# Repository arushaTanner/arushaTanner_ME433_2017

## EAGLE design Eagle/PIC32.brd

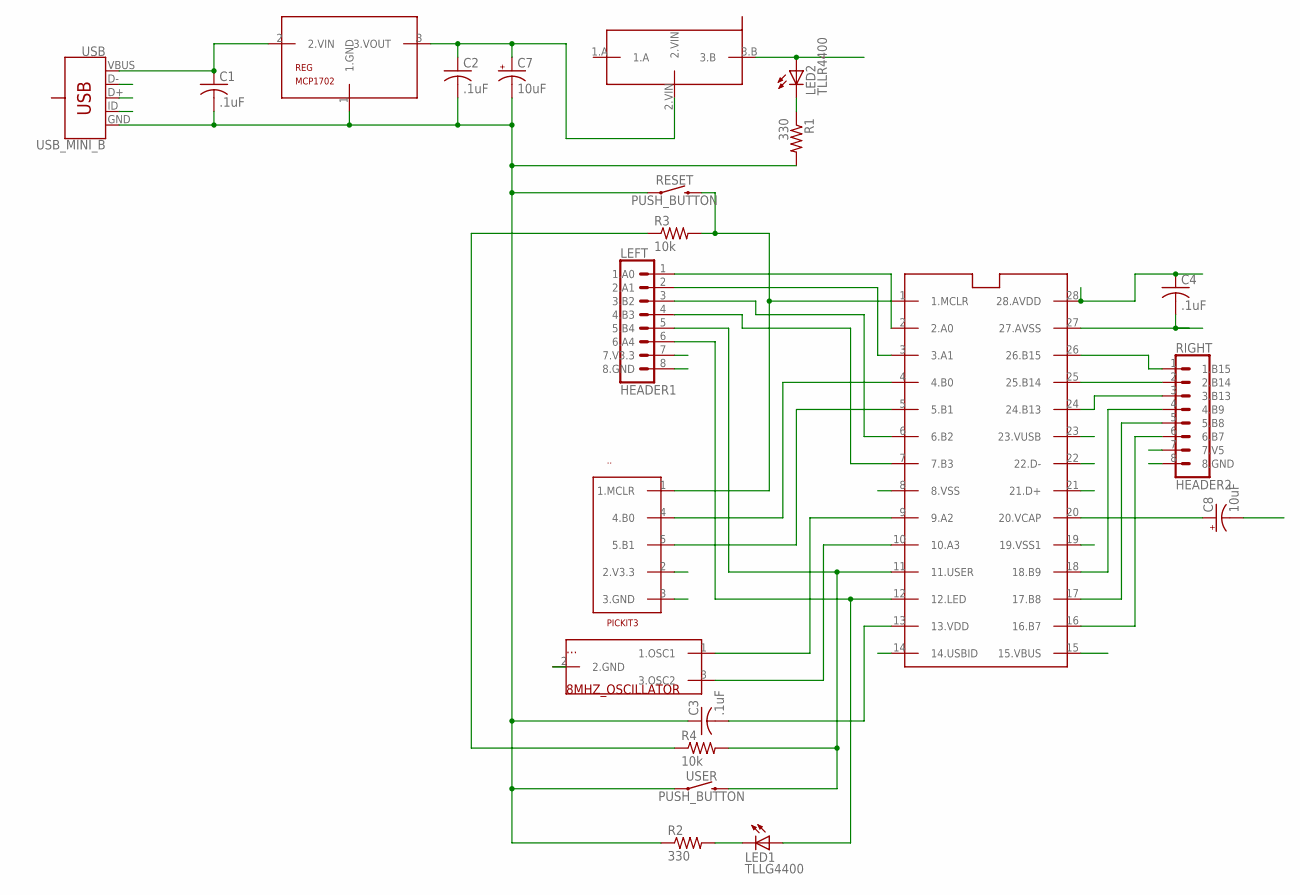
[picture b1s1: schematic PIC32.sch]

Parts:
..: PICKIT3; 1X05
...: 8MHZ_OSCILLATOR; 1X03
C1, C2, C3, C4: .1uF; C025-025X050
C7, C8: 10uF; E5-8,5
DIP_28: PIC32MX250F128_DIP; DIL28-3
LED1: TLLG4400; LED3MM
LED2: TLLR4400; LED3MM
LEFT: HEADER1; 1X08
R1, R2: 330; 0207/10
R3, R4: 10k; 0207/10
REG: MCP1702; TO92
RESET: PUSH_BUTTON; PB
RIGHT: HEADER2; 1X08
U$5: SLIDE_SWITCH
USB: USB_MINI_B; USB-MB-H
USER: PUSH_BUTTON; PB

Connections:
A0: DIP_28.2 (2.A0), LEFT.1 (1.A0)
A1: DIP_28.3 (3.A1), LEFT.2 (2.A1)
A2: ....1 (1.OSC1), DIP_28.9 (9.A2)
A3: ....3 (3.OSC2), DIP_28.10 (10.A3)
A4: DIP_28.12 (12.LED), LED1.A, LEFT.6 (6.A4)
B0: ...4 (4.B0), DIP_28.4 (4.B0)
B1: ...5 (5.B1), DIP_28.5 (5.B1)
B2: DIP_28.6 (6.B2), LEFT.3 (3.B2)
B3: DIP_28.7 (7.B3), LEFT.4 (4.B3)
B4: DIP_28.11 (11.USER), LEFT.5 (5.B4), R4.2, USER.2
B7: DIP_28.16 (16.B7), RIGHT.6 (6.B7)
B8: DIP_28.17 (17.B8), RIGHT.5 (5.B8)
B9: DIP_28.18 (18.B9), RIGHT.4 (4.B9)
B13: DIP_28.24 (24.B13), RIGHT.3 (3.B13)
B14: DIP_28.25 (25.B14), RIGHT.2 (2.B14)
B15: DIP_28.26 (26.B15), RIGHT.1 (1.B15)
D+: DIP_28.21 (21.D+), USB.D+ (3.D+)
D-: DIP_28.22 (22.D-), USB.D- (2.D-)
GND: ...3 (3.GND), ....2 (2.GND), C1.2, C2.2, C3.1, C4.2, C7.-, C8.-, DIP_28.8 (8.VSS), DIP_28.27 (27.AVSS), LEFT.8 (8.GND), R1.2, R2.1, REG.1 (1.GND), RESET.1, RIGHT.8 (8.GND), USB.GND (5.GND), USER.1
ID: DIP_28.14 (14.USBID), USB.ID (4.ID)
MCLR: ...1 (1.MCLR), DIP_28.1 (1.MCLR), R3.2, RESET.2
unnamed: C2.1, C7.+, REG.3 (3.VOUT), U$5.2.VIN
unnamed: LED2.K (C), R1.1
unnamed: LED1.K (C), R2.2
V3.3: ...2 (2.V3.3), C3.2, C4.1, DIP_28.13 (13.VDD), DIP_28.19 (19.VSS1), DIP_28.23 (23.VUSB), DIP_28.28 (28.AVDD), LED2.A, LEFT.7 (7.V3.3), R3.1, R4.1, U$5.3.B
VBUS: C1.1, DIP_28.15 (15.VBUS), REG.2 (2.VIN), RIGHT.7 (7.V5), USB.VBUS (1.VBUS)
VCAP: C8.+, DIP_28.20 (20.VCAP)

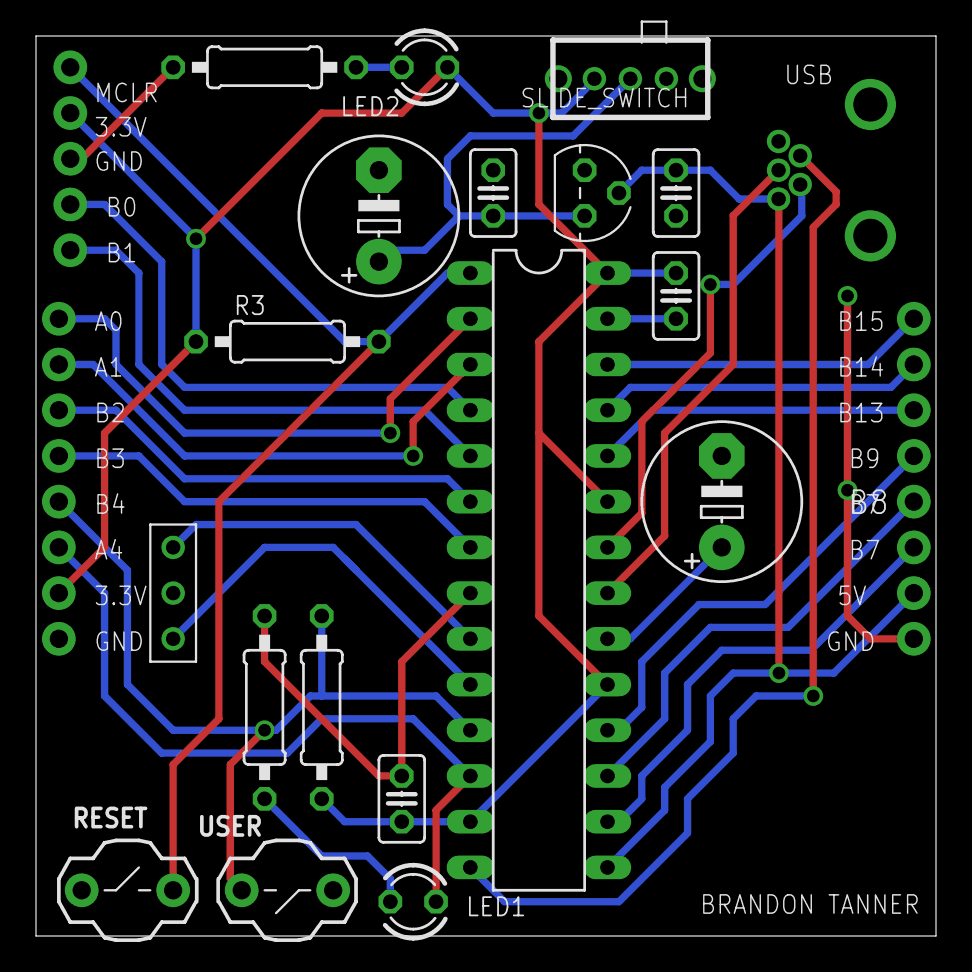
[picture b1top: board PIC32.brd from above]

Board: 2 copper layers, 50.0 x 50.0 mm, 22 parts (0 on the bottom side), 27 nets.

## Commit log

2017-03-29 adding HW1 folder to gitHub
2017-03-30 adding main.c
2017-03-30 completed HW1 with 1KHz LED and pushbutton
2017-03-30 Adding photos and videos
2017-04-03 Uploading sch, brd, and lbr files for Tuesday
2017-04-03 Uploading revised schematic and board without ground
2017-04-03 saving changes
2017-04-03 updated pushbuttons and usb connection
2017-04-06 uploading changes to eagle files and uploading HW3 with the Gerber files
2017-04-11 Uploading HW4 with the screen shot of triangle and sine waves
2017-04-13 uploading HW5. It doesn't work yet and I can't figure it out.
2017-04-18 HW with everything but the video. It works and is really fun!
2017-04-18 added the video with nick lecturing in the background
2017-04-22 Adding HW5 that almost works. It is so confusing and argh. It hates me...
2017-04-22 IT FINALLY WORKS. I FORGOT A SPACE!!%$##$$#@$#@. #codingprobs
2017-04-24 Uploading HW7. This is actually so cool. I am having a ton of fun!!!
2017-04-24 adding Harmony version of HW1. I am on a roll!
2017-04-24 finally caught up!!!
2017-05-03 Adding HW9. it works.
2017-05-03 Adding HW10 and base code for HW11. I haven't done the graphing or video for HW10 but the Code works
2017-05-04 Adding HW 9,10, and 11 meaning that I am all caught up. I just need to graph DSP stuff.
2017-05-09 Adding HW 12
